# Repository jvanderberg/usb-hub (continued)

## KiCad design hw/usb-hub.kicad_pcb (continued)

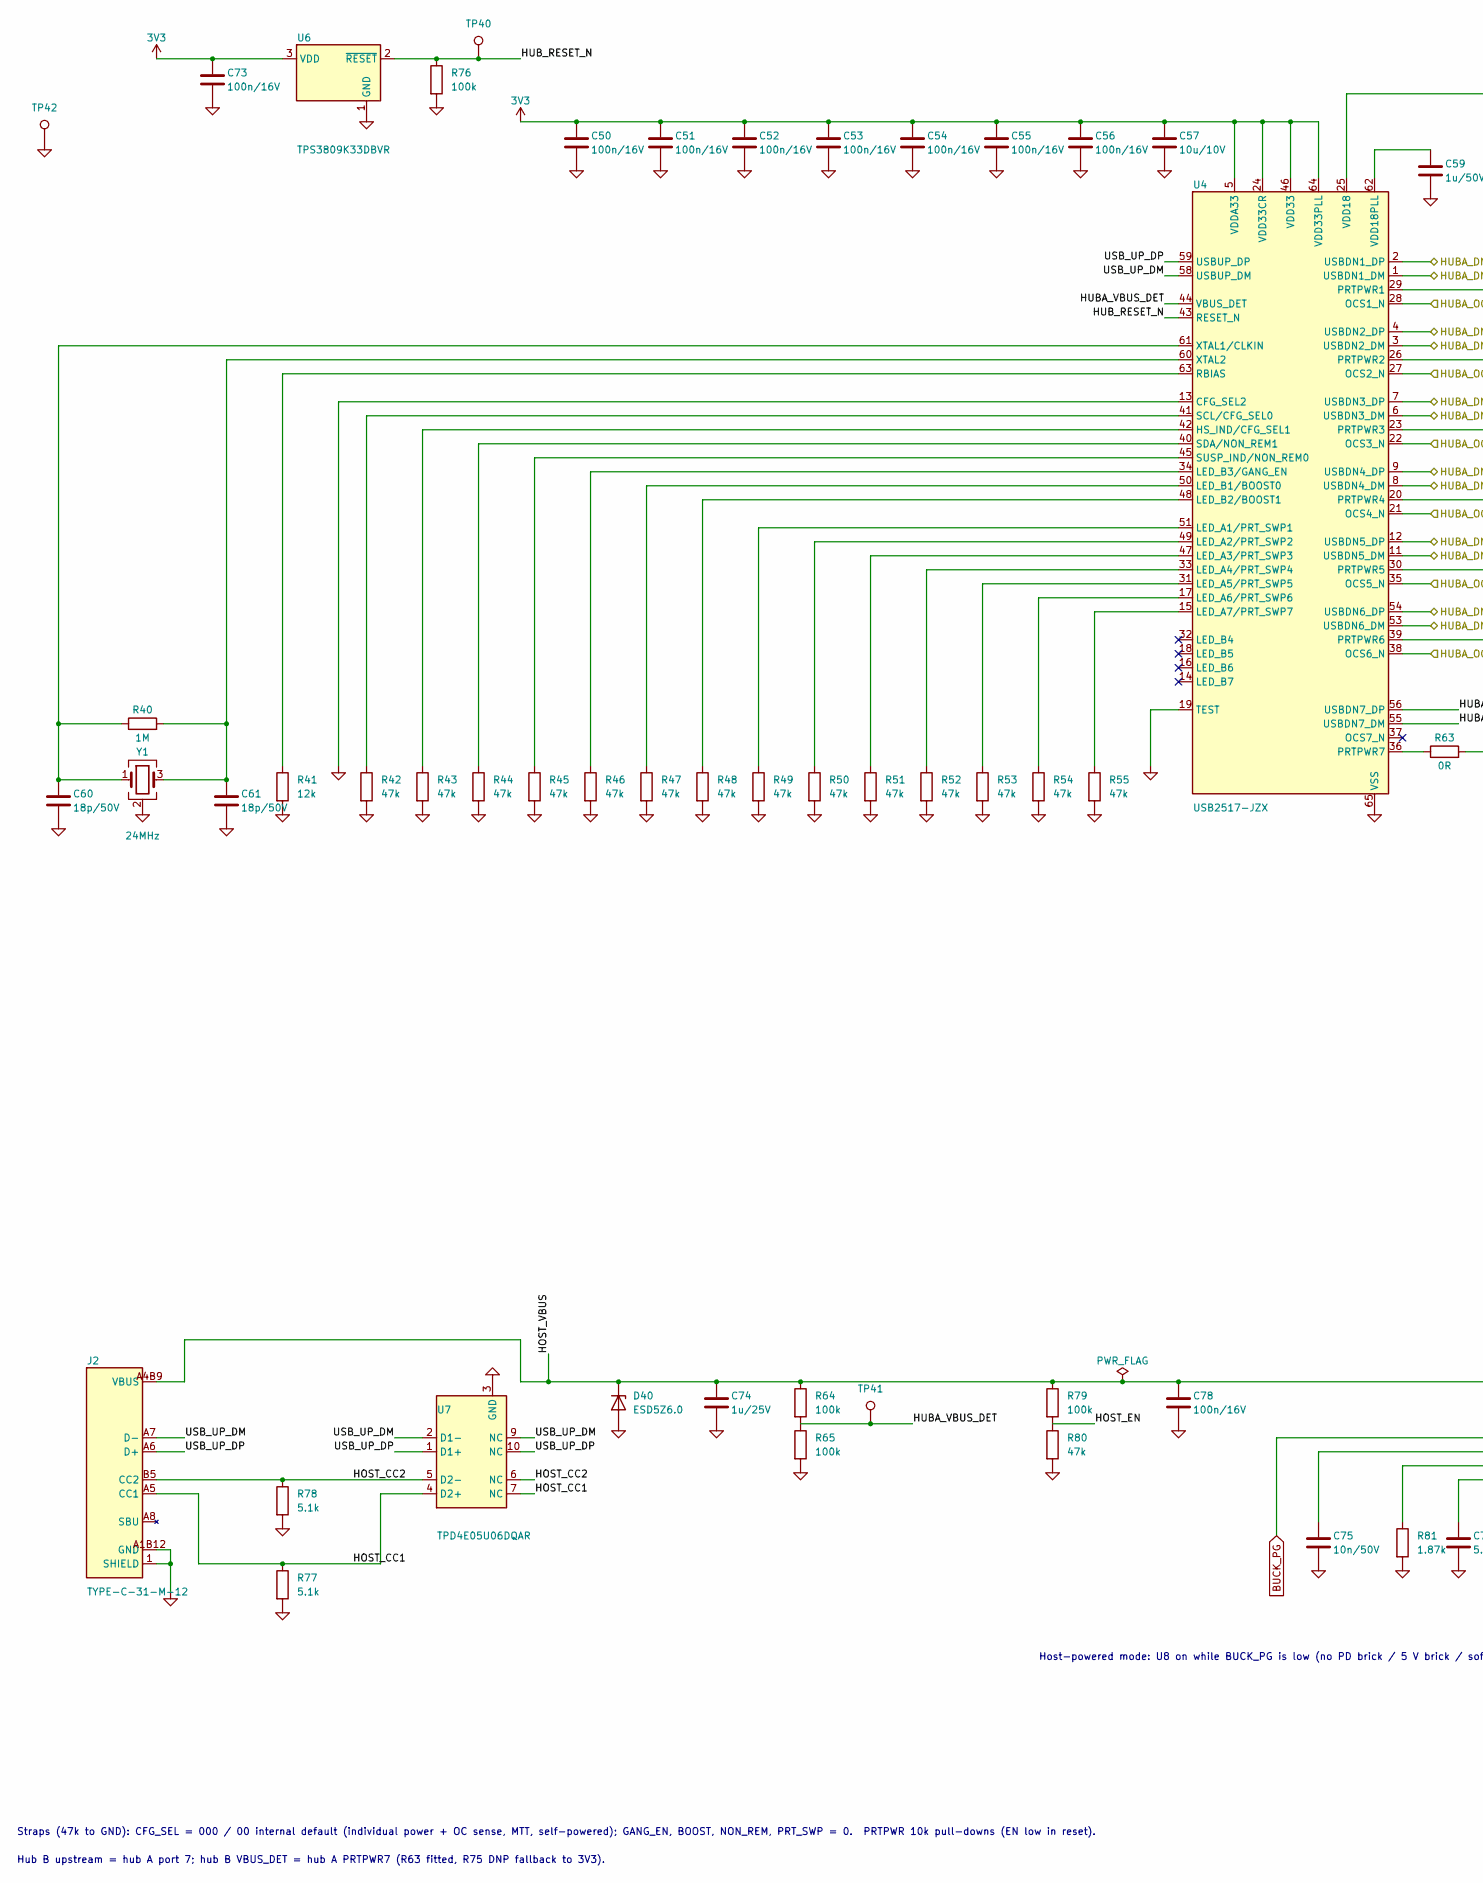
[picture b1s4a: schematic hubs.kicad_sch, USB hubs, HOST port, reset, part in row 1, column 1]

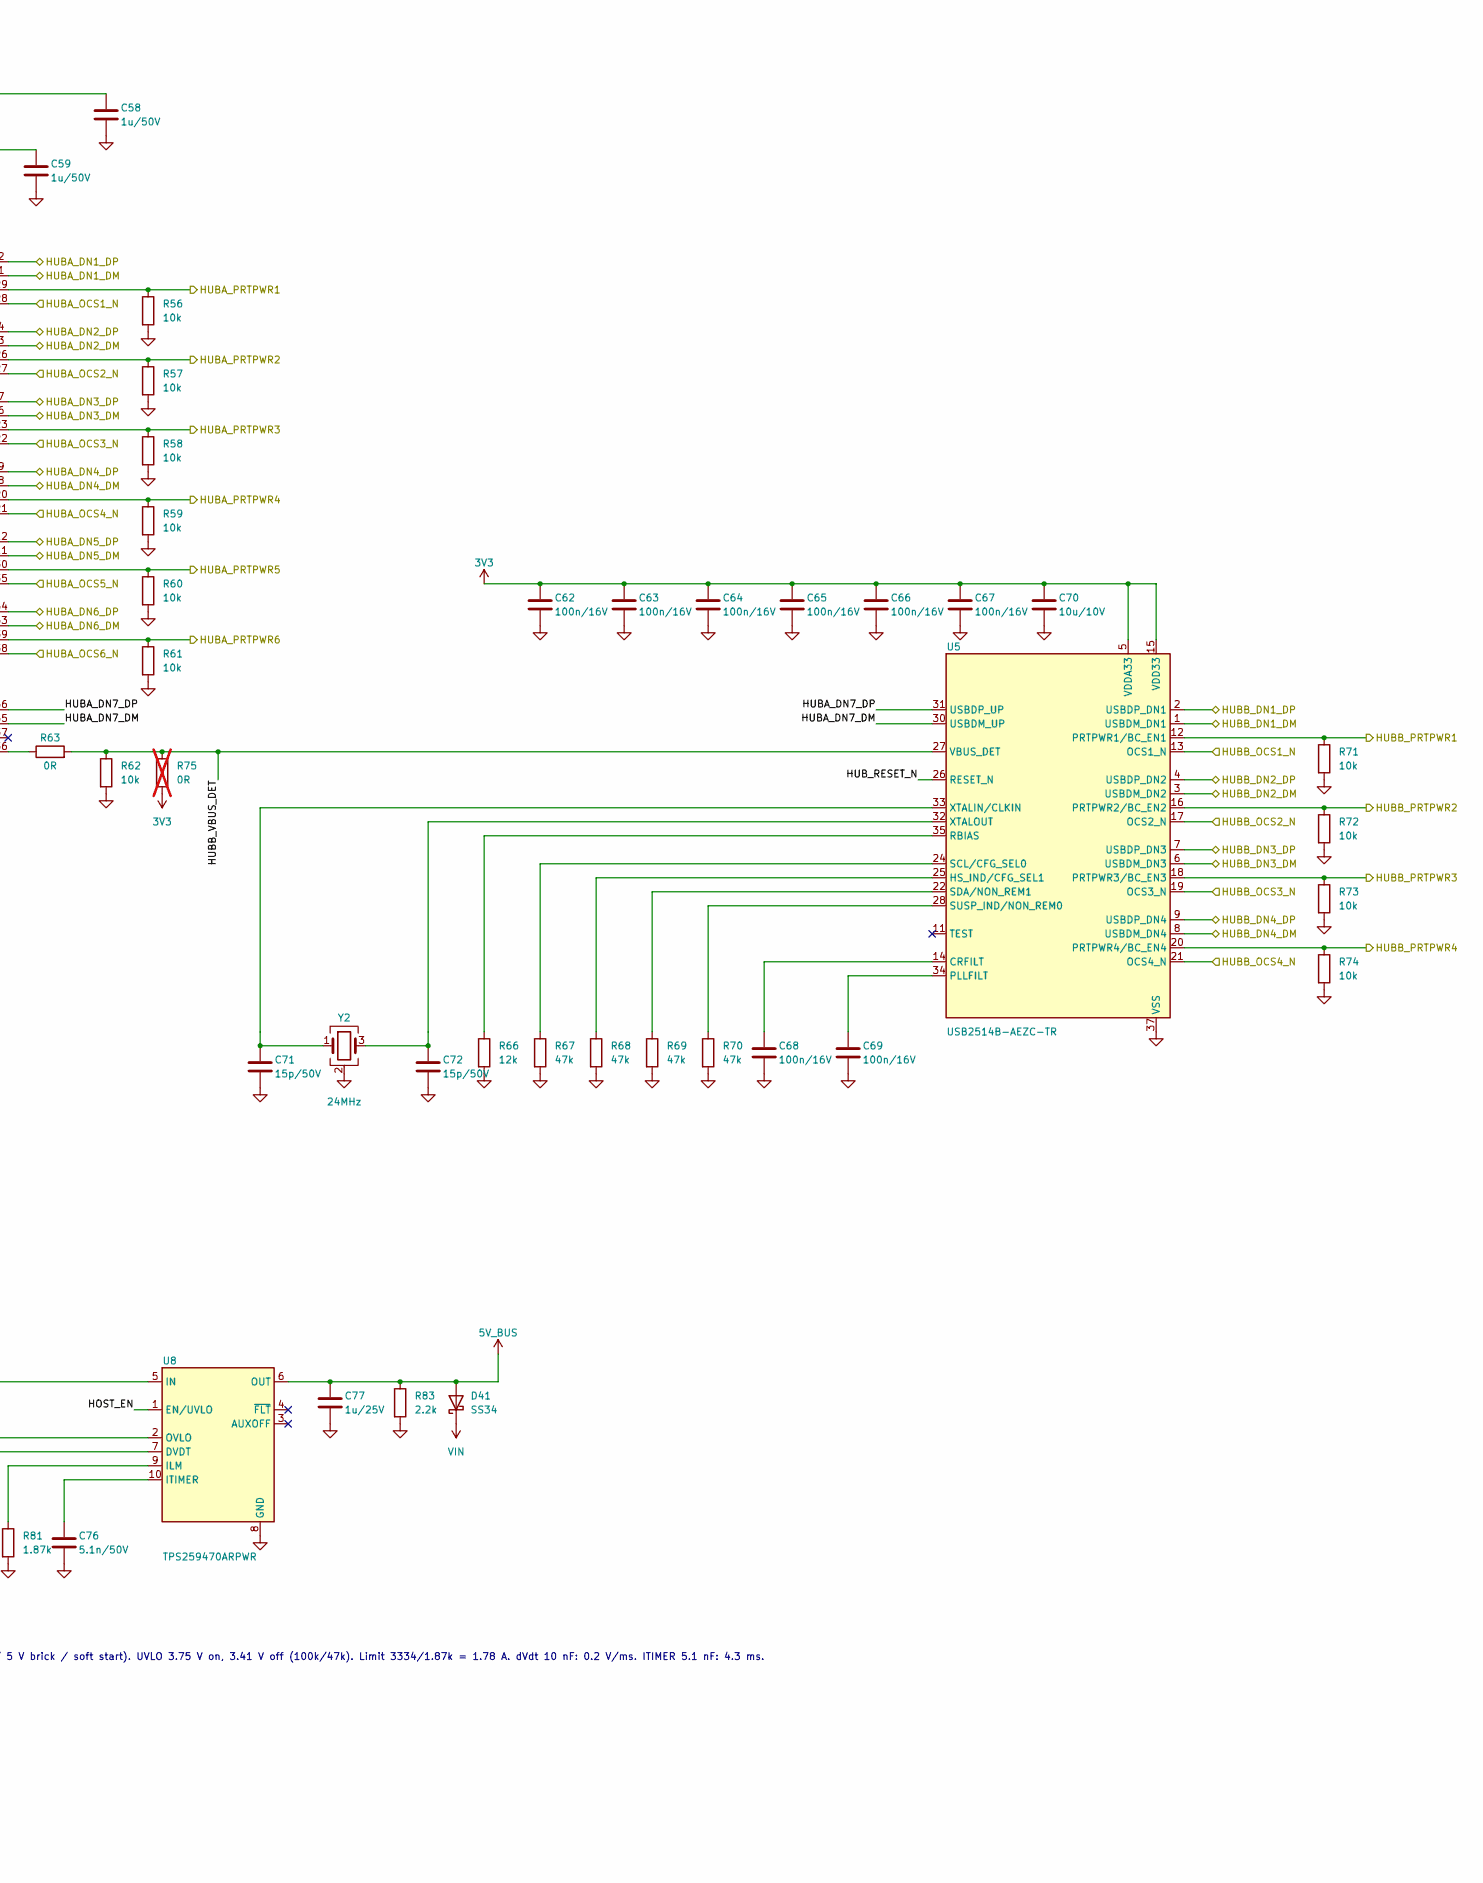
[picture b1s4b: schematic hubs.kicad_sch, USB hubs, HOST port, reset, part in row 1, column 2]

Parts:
C50, C51, C52, C53, C54, C55, C56, C62, C63, C64, C65, C66, C67, C68, C69, C73, C78: 100n/16V; CL05B104KO5NNNC; Manufacturer Part CL05B104KO5NNNC; LCSC C1525
C57, C70: 10u/10V; CL10A106KP8NNNC; Manufacturer Part CL10A106KP8NNNC; LCSC C19702
C58, C59: 1u/50V; CL10A105KB8NNNC; Manufacturer Part CL10A105KB8NNNC; LCSC C15849
C60, C61: 18p/50V; 0402CG180J500NT; Manufacturer Part 0402CG180J500NT; LCSC C1549
C71, C72: 15p/50V; 0402CG150J500NT; Manufacturer Part 0402CG150J500NT; LCSC C1548
C74, C77: 1u/25V; CL05A105KA5NQNC; Manufacturer Part CL05A105KA5NQNC; LCSC C52923
C75: 10n/50V; CL05B103KB5NNNC; Manufacturer Part CL05B103KB5NNNC; LCSC C15195
C76: 5.1n/50V; 0402B512K500NT; Manufacturer Part 0402B512K500NT; LCSC C47118429
D40: ESD5Z6.0; ESD5Z6_0T1G; Manufacturer Part ESD5Z6.0T1G; LCSC C82323
D41: SS34; SS34_C8678; Manufacturer Part SS34; LCSC C8678
J2: TYPE-C-31-M-12; Manufacturer Part TYPE-C-31-M-12; LCSC C165948
R40: 1M; 0402WGF1004TCE; Manufacturer Part 0402WGF1004TCE; LCSC C26083
R41, R66: 12k; 0402WGF1202TCE; Manufacturer Part 0402WGF1202TCE; LCSC C25752
R42, R43, R44, R45, R46, R47, R48, R49, R50, R51, R52, R53, R54, R55, R67, R68, R69, R70, R80: 47k; 0402WGF4702TCE; Manufacturer Part 0402WGF4702TCE; LCSC C25792
R56, R57, R58, R59, R60, R61, R62, R71, R72, R73, R74: 10k; 0402WGF1002TCE; Manufacturer Part 0402WGF1002TCE; LCSC C25744
R63: 0R; 0402WGF0000TCE; Manufacturer Part 0402WGF0000TCE; LCSC C17168
R64, R65, R76, R79: 100k; 0402WGF1003TCE; Manufacturer Part 0402WGF1003TCE; LCSC C25741
R75: 0R; 0402WGF0000TCE; Manufacturer Part 0402WGF0000TCE; LCSC C17168; not fitted
R77, R78: 5.1k; 0402WGF5101TCE; Manufacturer Part 0402WGF5101TCE; LCSC C25905
R81: 1.87k; 0402WGF1871TCE; Manufacturer Part 0402WGF1871TCE; LCSC C270633
R83: 2.2k; 0402WGF2201TCE; Manufacturer Part 0402WGF2201TCE; LCSC C25879
TP40: HUB_RESET_N; TestPoint_Pad_D1.0mm
TP41: VBUS_DET; TestPoint_Pad_D1.0mm
TP42: GND; TestPoint_Pad_D1.0mm
U4: USB2517-JZX; USB2517-JZX_ThermalVias; Manufacturer Part USB2517-JZX; LCSC C1521556
U5: USB2514B-AEZC-TR; USB2514B-AEZC-TR_ThermalVias; Manufacturer Part USB2514B-AEZC-TR; LCSC C16251
U6: TPS3809K33DBVR; Manufacturer Part TPS3809K33DBVR; LCSC C61364
U7: TPD4E05U06DQAR; TPD4E05U06DQAR_C138714; Manufacturer Part TPD4E05U06DQAR; LCSC C138714
U8: TPS259470ARPWR; TPS259470ARPWR_TILand; Manufacturer Part TPS259470ARPWR; LCSC C3662799
Y1, Y2: 24MHz; X322524MOB4SI; Manufacturer Part X322524MOB4SI; LCSC C70590

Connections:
3V3: C50.1, C51.1, C52.1, C53.1, C54.1, C55.1, C56.1, C57.1, C62.1, C63.1, C64.1, C65.1, C66.1, C67.1, C70.1, C73.1, R75.2, U4.5 (VDDA33), U4.10 (VDDA33), U4.24 (VDD33CR), U4.46 (VDD33), U4.52 (VDDA33), U4.57 (VDDA33), U4.64 (VDD33PLL), U5.5 (VDDA33), U5.10 (VDDA33), U5.15 (VDD33), U5.23 (VDD33), U5.29 (VDDA33), U5.36 (VDDA33), U6.3 (VDD); also elsewhere on the board
5V_BUS: C77.1, D41.2 (A), R83.1, U8.6 (OUT); also elsewhere on the board
/HUBA_DN1_DM: U4.1 (USBDN1_DM); also elsewhere on the board
/HUBA_DN1_DP: U4.2 (USBDN1_DP); also elsewhere on the board
/HUBA_DN2_DM: U4.3 (USBDN2_DM); also elsewhere on the board
/HUBA_DN2_DP: U4.4 (USBDN2_DP); also elsewhere on the board
/HUBA_DN3_DM: U4.6 (USBDN3_DM); also elsewhere on the board
/HUBA_DN3_DP: U4.7 (USBDN3_DP); also elsewhere on the board
/HUBA_DN4_DM: U4.8 (USBDN4_DM); also elsewhere on the board
/HUBA_DN4_DP: U4.9 (USBDN4_DP); also elsewhere on the board
/HUBA_DN5_DM: U4.11 (USBDN5_DM); also elsewhere on the board
/HUBA_DN5_DP: U4.12 (USBDN5_DP); also elsewhere on the board
/HUBA_DN6_DM: U4.53 (USBDN6_DM); also elsewhere on the board
/HUBA_DN6_DP: U4.54 (USBDN6_DP); also elsewhere on the board
/HUBA_OCS1_N: U4.28 (OCS1_N); also elsewhere on the board
/HUBA_OCS2_N: U4.27 (OCS2_N); also elsewhere on the board
/HUBA_OCS3_N: U4.22 (OCS3_N); also elsewhere on the board
/HUBA_OCS4_N: U4.21 (OCS4_N); also elsewhere on the board
/HUBA_OCS5_N: U4.35 (OCS5_N); also elsewhere on the board
/HUBA_OCS6_N: U4.38 (OCS6_N); also elsewhere on the board
/HUBA_PRTPWR1: R56.1, U4.29 (PRTPWR1); also elsewhere on the board
/HUBA_PRTPWR2: R57.1, U4.26 (PRTPWR2); also elsewhere on the board
/HUBA_PRTPWR3: R58.1, U4.23 (PRTPWR3); also elsewhere on the board
/HUBA_PRTPWR4: R59.1, U4.20 (PRTPWR4); also elsewhere on the board
/HUBA_PRTPWR5: R60.1, U4.30 (PRTPWR5); also elsewhere on the board
/HUBA_PRTPWR6: R61.1, U4.39 (PRTPWR6); also elsewhere on the board
/HUBB_DN1_DM: U5.1 (USBDM_DN1); also elsewhere on the board
/HUBB_DN1_DP: U5.2 (USBDP_DN1); also elsewhere on the board
/HUBB_DN2_DM: U5.3 (USBDM_DN2); also elsewhere on the board
/HUBB_DN2_DP: U5.4 (USBDP_DN2); also elsewhere on the board
/HUBB_DN3_DM: U5.6 (USBDM_DN3); also elsewhere on the board
/HUBB_DN3_DP: U5.7 (USBDP_DN3); also elsewhere on the board
/HUBB_DN4_DM: U5.8 (USBDM_DN4); also elsewhere on the board
/HUBB_DN4_DP: U5.9 (USBDP_DN4); also elsewhere on the board
/HUBB_OCS1_N: U5.13 (OCS1_N); also elsewhere on the board
/HUBB_OCS2_N: U5.17 (OCS2_N); also elsewhere on the board
/HUBB_OCS3_N: U5.19 (OCS3_N); also elsewhere on the board
/HUBB_OCS4_N: U5.21 (OCS4_N); also elsewhere on the board
/HUBB_PRTPWR1: R71.1, U5.12 (PRTPWR1/BC_EN1); also elsewhere on the board
/HUBB_PRTPWR2: R72.1, U5.16 (PRTPWR2/BC_EN2); also elsewhere on the board
/HUBB_PRTPWR3: R73.1, U5.18 (PRTPWR3/BC_EN3); also elsewhere on the board
/HUBB_PRTPWR4: R74.1, U5.20 (PRTPWR4/BC_EN4); also elsewhere on the board
/hubs/HOST_CC1: J2.A5 (CC1), R77.1, U7.4 (D2+), U7.7 (NC)
/hubs/HOST_CC2: J2.B5 (CC2), R78.1, U7.5 (D2-), U7.6 (NC)
/hubs/HOST_EN: R79.2, R80.1, U8.1 (EN/UVLO)
/hubs/HOST_VBUS: C74.1, C78.1, D40.1 (K), J2.A4B9 (VBUS), J2.B4A9 (VBUS), R64.1, R79.1, U8.5 (IN)
/hubs/HUBA_DN7_DM: U4.55 (USBDN7_DM), U5.30 (USBDM_UP)
/hubs/HUBA_DN7_DP: U4.56 (USBDN7_DP), U5.31 (USBDP_UP)
/hubs/HUBA_VBUS_DET: R64.2, R65.1, TP41.1 (1_1), U4.44 (VBUS_DET)
/hubs/HUBB_VBUS_DET: R62.1, R63.2, R75.1, U5.27 (VBUS_DET)
/hubs/HUB_RESET_N: R76.1, TP40.1 (1_1), U4.43 (RESET_N), U5.26 (RESET_N), U6.2 (~RESET)
/hubs/USB_UP_DM: J2.A7 (D-), J2.B7 (D-), U4.58 (USBUP_DM), U7.2 (D1-), U7.9 (NC)
/hubs/USB_UP_DP: J2.A6 (D+), J2.B6 (D+), U4.59 (USBUP_DP), U7.1 (D1+), U7.10 (NC)
BUCK_PG: U8.2 (OVLO); also elsewhere on the board
GND: C50.2, C51.2, C52.2, C53.2, C54.2, C55.2, C56.2, C57.2, C58.2, C59.2, C60.2, C61.2, C62.2, C63.2, C64.2, C65.2, C66.2, C67.2, C68.2, C69.2, C70.2, C71.2, C72.2, C73.2, C74.2, C75.2, C76.2, C77.2, C78.2, D40.2 (A), J2.1 (SHIELD), J2.2 (SHIELD), J2.3 (SHIELD), J2.4 (SHIELD), J2.A1B12 (GND), J2.B1A12 (GND), R41.2, R42.2, R43.2, R44.2, R45.2, R46.2, R47.2, R48.2, R49.2, R50.2, R51.2, R52.2, R53.2, R54.2, R55.2, R56.2, R57.2, R58.2, R59.2, R60.2, R61.2, R62.2, R65.2, R66.2, R67.2, R68.2, R69.2, R70.2, R71.2, R72.2, R73.2, R74.2, R76.2, R77.2, R78.2, R80.2, R81.2, R83.2, TP42.1 (1_1), U4.13 (CFG_SEL2), U4.19 (TEST), U4.65 (VSS), U5.37 (VSS), U6.1 (GND), U7.3 (GND), U7.8 (GND), U8.8 (GND), Y1.2 (G), Y1.4 (G), Y2.2 (G), Y2.4 (G); also elsewhere on the board
unnamed: R43.1, U4.42 (HS_IND/CFG_SEL1)
unnamed: R49.1, U4.51 (LED_A1/PRT_SWP1)
unnamed: R50.1, U4.49 (LED_A2/PRT_SWP2)
unnamed: R51.1, U4.47 (LED_A3/PRT_SWP3)
unnamed: R52.1, U4.33 (LED_A4/PRT_SWP4)
unnamed: R53.1, U4.31 (LED_A5/PRT_SWP5)
unnamed: R54.1, U4.17 (LED_A6/PRT_SWP6)
unnamed: R55.1, U4.15 (LED_A7/PRT_SWP7)
unnamed: R47.1, U4.50 (LED_B1/BOOST0)
unnamed: R48.1, U4.48 (LED_B2/BOOST1)
unnamed: R46.1, U4.34 (LED_B3/GANG_EN)
unnamed: R63.1, U4.36 (PRTPWR7)
unnamed: R41.1, U4.63 (RBIAS)
unnamed: R42.1, U4.41 (SCL/CFG_SEL0)
unnamed: R44.1, U4.40 (SDA/NON_REM1)
unnamed: R45.1, U4.45 (SUSP_IND/NON_REM0)
unnamed: C58.1, U4.25 (VDD18)
unnamed: C59.1, U4.62 (VDD18PLL)
unnamed: C60.1, R40.1, U4.61 (XTAL1/CLKIN), Y1.1
unnamed: C61.1, R40.2, U4.60 (XTAL2), Y1.3
unnamed: C68.1, U5.14 (CRFILT)
unnamed: R68.1, U5.25 (HS_IND/CFG_SEL1)
unnamed: C69.1, U5.34 (PLLFILT)
unnamed: R66.1, U5.35 (RBIAS)
unnamed: R67.1, U5.24 (SCL/CFG_SEL0)
unnamed: R69.1, U5.22 (SDA/NON_REM1)
unnamed: R70.1, U5.28 (SUSP_IND/NON_REM0)
unnamed: C71.1, U5.33 (XTALIN/CLKIN), Y2.1
unnamed: C72.1, U5.32 (XTALOUT), Y2.3
unnamed: C75.1, U8.7 (DVDT)
unnamed: R81.1, U8.9 (ILM)
unnamed: C76.1, U8.10 (ITIMER)
VIN: D41.1 (K); also elsewhere on the board

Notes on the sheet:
Host-powered mode: U8 on while BUCK_PG is low (no PD brick / 5 V brick / soft start). UVLO 3.75 V on, 3.41 V off (100k/47k). Limit 3334/1.87k = 1.78 A. dVdt 10 nF: 0.2 V/ms. ITIMER 5.1 nF: 4.3 ms.
Straps (47k to GND): CFG_SEL = 000 / 00 internal default (individual power + OC sense, MTT, self-powered); GANG_EN, BOOST, NON_REM, PRT_SWP = 0. PRTPWR 10k pull-downs (EN low in reset).
Hub B upstream = hub A port 7; hub B VBUS_DET = hub A PRTPWR7 (R63 fitted, R75 DNP fallback to 3V3).

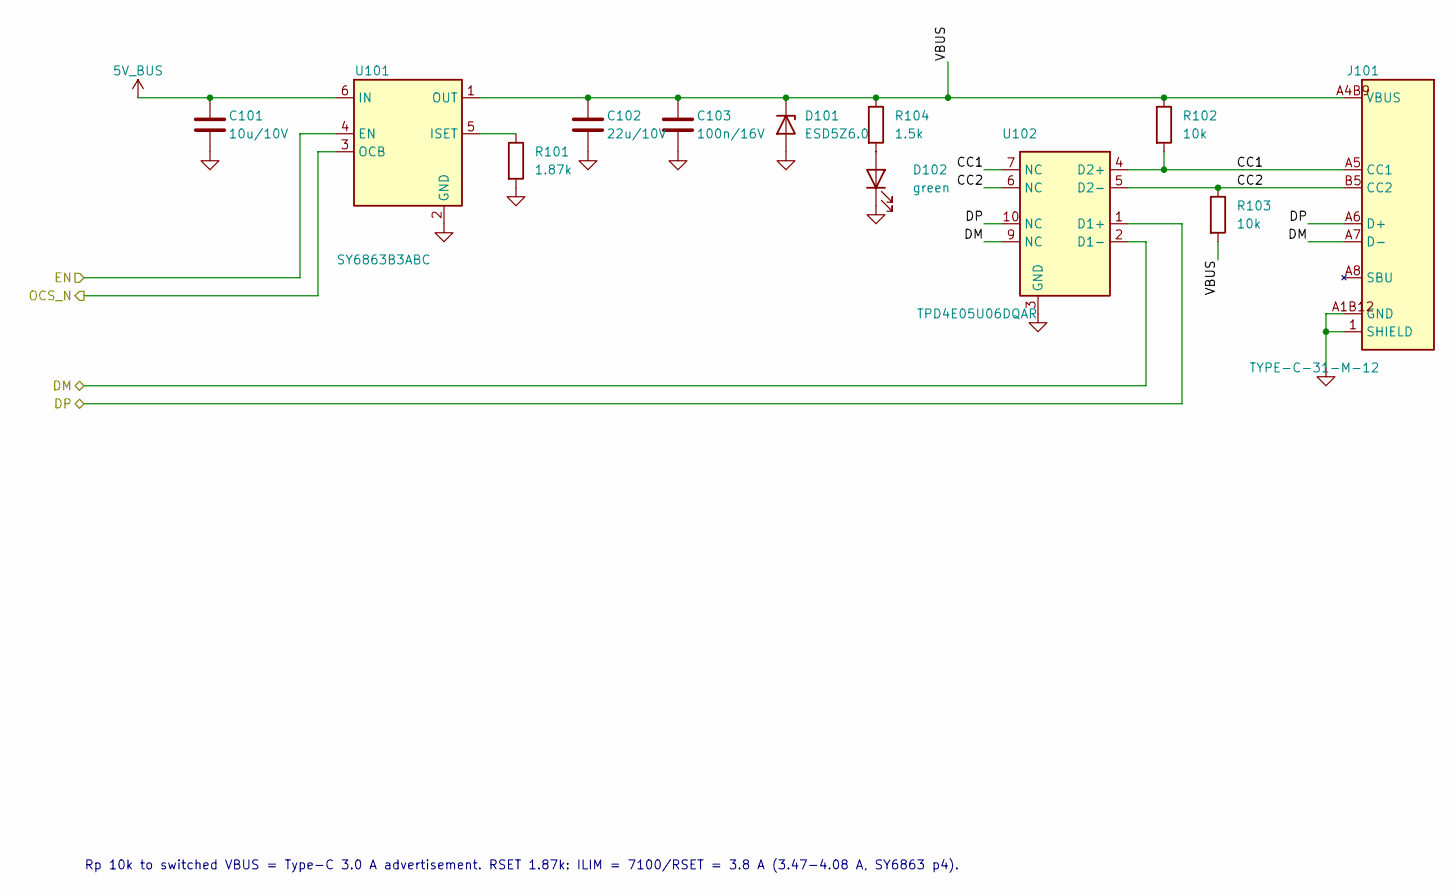
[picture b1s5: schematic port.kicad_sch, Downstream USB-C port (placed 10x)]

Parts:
C101: 10u/10V; CL10A106KP8NNNC; Manufacturer Part CL10A106KP8NNNC; LCSC C19702
C102: 22u/10V; CL10A226MQ8NRNC; Manufacturer Part CL10A226MQ8NRNC; LCSC C59461
C103: 100n/16V; CL05B104KO5NNNC; Manufacturer Part CL05B104KO5NNNC; LCSC C1525
D101: ESD5Z6.0; ESD5Z6_0T1G; Manufacturer Part ESD5Z6.0T1G; LCSC C82323
D102: green; 0603_Green_509-620mcd; Manufacturer Part KT-0603G; LCSC C12624
J101: TYPE-C-31-M-12; Manufacturer Part TYPE-C-31-M-12; LCSC C165948
R101: 1.87k; 0402WGF1871TCE; Manufacturer Part 0402WGF1871TCE; LCSC C270633
R102, R103: 10k; 0402WGF1002TCE; Manufacturer Part 0402WGF1002TCE; LCSC C25744
R104: 1.5k; 0402WGF1501TCE; Manufacturer Part 0402WGF1501TCE; LCSC C25867
U101: SY6863B3ABC; Manufacturer Part SY6863B3ABC; LCSC C2687365
U102: TPD4E05U06DQAR; TPD4E05U06DQAR_C138714; Manufacturer Part TPD4E05U06DQAR; LCSC C138714

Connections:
5V_BUS: C101.1, U101.6 (IN); also elsewhere on the board
/HUBA_DN1_DM: J101.A7 (D-), J101.B7 (D-), U102.2 (D1-), U102.9 (NC); also elsewhere on the board
/HUBA_DN1_DP: J101.A6 (D+), J101.B6 (D+), U102.1 (D1+), U102.10 (NC); also elsewhere on the board
/HUBA_OCS1_N: U101.3 (OCB); also elsewhere on the board
/HUBA_PRTPWR1: U101.4 (EN); also elsewhere on the board
/port1/CC1: J101.A5 (CC1), R102.2, U102.4 (D2+), U102.7 (NC)
/port1/CC2: J101.B5 (CC2), R103.1, U102.5 (D2-), U102.6 (NC)
/port1/VBUS: C102.1, C103.1, D101.1 (K), J101.A4B9 (VBUS), J101.B4A9 (VBUS), R102.1, R103.2, R104.1, U101.1 (OUT)
GND: C101.2, C102.2, C103.2, D101.2 (A), D102.1 (K), J101.1 (SHIELD), J101.2 (SHIELD), J101.3 (SHIELD), J101.4 (SHIELD), J101.A1B12 (GND), J101.B1A12 (GND), R101.2, U101.2 (GND), U102.3 (GND), U102.8 (GND); also elsewhere on the board
unnamed: D102.2 (A), R104.2
unnamed: R101.1, U101.5 (ISET)

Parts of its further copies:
C201, C301, C401, C501, C601, C701, C801, C901, C1001: 10u/10V; CL10A106KP8NNNC; Manufacturer Part CL10A106KP8NNNC; LCSC C19702
C202, C302, C402, C502, C602, C702, C802, C902, C1002: 22u/10V; CL10A226MQ8NRNC; Manufacturer Part CL10A226MQ8NRNC; LCSC C59461
C203, C303, C403, C503, C603, C703, C803, C903, C1003: 100n/16V; CL05B104KO5NNNC; Manufacturer Part CL05B104KO5NNNC; LCSC C1525
D201, D301, D401, D501, D601, D701, D801, D901, D1001: ESD5Z6.0; ESD5Z6_0T1G; Manufacturer Part ESD5Z6.0T1G; LCSC C82323
D202, D302, D402, D502, D602, D702, D802, D902, D1002: green; 0603_Green_509-620mcd; Manufacturer Part KT-0603G; LCSC C12624
J201, J301, J401, J501, J601, J701, J801, J901, J1001: TYPE-C-31-M-12; Manufacturer Part TYPE-C-31-M-12; LCSC C165948
R201, R301, R401, R501, R601, R701, R801, R901, R1001: 1.87k; 0402WGF1871TCE; Manufacturer Part 0402WGF1871TCE; LCSC C270633
R202, R203, R302, R303, R402, R403, R502, R503, R602, R603, R702, R703, R802, R803, R902, R903, R1002, R1003: 10k; 0402WGF1002TCE; Manufacturer Part 0402WGF1002TCE; LCSC C25744
R204, R304, R404, R504, R604, R704, R804, R904, R1004: 1.5k; 0402WGF1501TCE; Manufacturer Part 0402WGF1501TCE; LCSC C25867
U201, U301, U401, U501, U601, U701, U801, U901, U1001: SY6863B3ABC; Manufacturer Part SY6863B3ABC; LCSC C2687365
U202, U302, U402, U502, U602, U702, U802, U902, U1002: TPD4E05U06DQAR; TPD4E05U06DQAR_C138714; Manufacturer Part TPD4E05U06DQAR; LCSC C138714

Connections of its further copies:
5V_BUS: C201.1, C301.1, C401.1, C501.1, C601.1, C701.1, C801.1, C901.1, C1001.1, U201.6 (IN), U301.6 (IN), U401.6 (IN), U501.6 (IN), U601.6 (IN), U701.6 (IN), U801.6 (IN), U901.6 (IN), U1001.6 (IN); also elsewhere on the board
/HUBA_DN2_DM: J201.A7 (D-), J201.B7 (D-), U202.2 (D1-), U202.9 (NC); also elsewhere on the board
/HUBA_DN2_DP: J201.A6 (D+), J201.B6 (D+), U202.1 (D1+), U202.10 (NC); also elsewhere on the board
/HUBA_DN3_DM: J301.A7 (D-), J301.B7 (D-), U302.2 (D1-), U302.9 (NC); also elsewhere on the board
/HUBA_DN3_DP: J301.A6 (D+), J301.B6 (D+), U302.1 (D1+), U302.10 (NC); also elsewhere on the board
/HUBA_DN4_DM: J401.A7 (D-), J401.B7 (D-), U402.2 (D1-), U402.9 (NC); also elsewhere on the board
/HUBA_DN4_DP: J401.A6 (D+), J401.B6 (D+), U402.1 (D1+), U402.10 (NC); also elsewhere on the board
/HUBA_DN5_DM: J501.A7 (D-), J501.B7 (D-), U502.2 (D1-), U502.9 (NC); also elsewhere on the board
/HUBA_DN5_DP: J501.A6 (D+), J501.B6 (D+), U502.1 (D1+), U502.10 (NC); also elsewhere on the board
/HUBA_DN6_DM: J601.A7 (D-), J601.B7 (D-), U602.2 (D1-), U602.9 (NC); also elsewhere on the board
/HUBA_DN6_DP: J601.A6 (D+), J601.B6 (D+), U602.1 (D1+), U602.10 (NC); also elsewhere on the board
/HUBA_OCS2_N: U201.3 (OCB); also elsewhere on the board
/HUBA_OCS3_N: U301.3 (OCB); also elsewhere on the board
/HUBA_OCS4_N: U401.3 (OCB); also elsewhere on the board
/HUBA_OCS5_N: U501.3 (OCB); also elsewhere on the board
/HUBA_OCS6_N: U601.3 (OCB); also elsewhere on the board
/HUBA_PRTPWR2: U201.4 (EN); also elsewhere on the board
/HUBA_PRTPWR3: U301.4 (EN); also elsewhere on the board
/HUBA_PRTPWR4: U401.4 (EN); also elsewhere on the board
/HUBA_PRTPWR5: U501.4 (EN); also elsewhere on the board
/HUBA_PRTPWR6: U601.4 (EN); also elsewhere on the board
/HUBB_DN1_DM: J701.A7 (D-), J701.B7 (D-), U702.2 (D1-), U702.9 (NC); also elsewhere on the board
/HUBB_DN1_DP: J701.A6 (D+), J701.B6 (D+), U702.1 (D1+), U702.10 (NC); also elsewhere on the board
/HUBB_DN2_DM: J801.A7 (D-), J801.B7 (D-), U802.2 (D1-), U802.9 (NC); also elsewhere on the board
/HUBB_DN2_DP: J801.A6 (D+), J801.B6 (D+), U802.1 (D1+), U802.10 (NC); also elsewhere on the board
/HUBB_DN3_DM: J901.A7 (D-), J901.B7 (D-), U902.2 (D1-), U902.9 (NC); also elsewhere on the board
/HUBB_DN3_DP: J901.A6 (D+), J901.B6 (D+), U902.1 (D1+), U902.10 (NC); also elsewhere on the board
/HUBB_DN4_DM: J1001.A7 (D-), J1001.B7 (D-), U1002.2 (D1-), U1002.9 (NC); also elsewhere on the board
/HUBB_DN4_DP: J1001.A6 (D+), J1001.B6 (D+), U1002.1 (D1+), U1002.10 (NC); also elsewhere on the board
/HUBB_OCS1_N: U701.3 (OCB); also elsewhere on the board
/HUBB_OCS2_N: U801.3 (OCB); also elsewhere on the board
/HUBB_OCS3_N: U901.3 (OCB); also elsewhere on the board
/HUBB_OCS4_N: U1001.3 (OCB); also elsewhere on the board
/HUBB_PRTPWR1: U701.4 (EN); also elsewhere on the board
/HUBB_PRTPWR2: U801.4 (EN); also elsewhere on the board
/HUBB_PRTPWR3: U901.4 (EN); also elsewhere on the board
/HUBB_PRTPWR4: U1001.4 (EN); also elsewhere on the board
/port2/CC1: J201.A5 (CC1), R202.2, U202.4 (D2+), U202.7 (NC)
/port2/CC2: J201.B5 (CC2), R203.1, U202.5 (D2-), U202.6 (NC)
/port2/VBUS: C202.1, C203.1, D201.1 (K), J201.A4B9 (VBUS), J201.B4A9 (VBUS), R202.1, R203.2, R204.1, U201.1 (OUT)
/port3/CC1: J301.A5 (CC1), R302.2, U302.4 (D2+), U302.7 (NC)
/port3/CC2: J301.B5 (CC2), R303.1, U302.5 (D2-), U302.6 (NC)
/port3/VBUS: C302.1, C303.1, D301.1 (K), J301.A4B9 (VBUS), J301.B4A9 (VBUS), R302.1, R303.2, R304.1, U301.1 (OUT)
/port4/CC1: J401.A5 (CC1), R402.2, U402.4 (D2+), U402.7 (NC)
/port4/CC2: J401.B5 (CC2), R403.1, U402.5 (D2-), U402.6 (NC)
/port4/VBUS: C402.1, C403.1, D401.1 (K), J401.A4B9 (VBUS), J401.B4A9 (VBUS), R402.1, R403.2, R404.1, U401.1 (OUT)
/port5/CC1: J501.A5 (CC1), R502.2, U502.4 (D2+), U502.7 (NC)
/port5/CC2: J501.B5 (CC2), R503.1, U502.5 (D2-), U502.6 (NC)
/port5/VBUS: C502.1, C503.1, D501.1 (K), J501.A4B9 (VBUS), J501.B4A9 (VBUS), R502.1, R503.2, R504.1, U501.1 (OUT)
/port6/CC1: J601.A5 (CC1), R602.2, U602.4 (D2+), U602.7 (NC)
/port6/CC2: J601.B5 (CC2), R603.1, U602.5 (D2-), U602.6 (NC)
/port6/VBUS: C602.1, C603.1, D601.1 (K), J601.A4B9 (VBUS), J601.B4A9 (VBUS), R602.1, R603.2, R604.1, U601.1 (OUT)
/port7/CC1: J701.A5 (CC1), R702.2, U702.4 (D2+), U702.7 (NC)
/port7/CC2: J701.B5 (CC2), R703.1, U702.5 (D2-), U702.6 (NC)
/port7/VBUS: C702.1, C703.1, D701.1 (K), J701.A4B9 (VBUS), J701.B4A9 (VBUS), R702.1, R703.2, R704.1, U701.1 (OUT)
/port8/CC1: J801.A5 (CC1), R802.2, U802.4 (D2+), U802.7 (NC)
/port8/CC2: J801.B5 (CC2), R803.1, U802.5 (D2-), U802.6 (NC)
/port8/VBUS: C802.1, C803.1, D801.1 (K), J801.A4B9 (VBUS), J801.B4A9 (VBUS), R802.1, R803.2, R804.1, U801.1 (OUT)
/port9/CC1: J901.A5 (CC1), R902.2, U902.4 (D2+), U902.7 (NC)
/port9/CC2: J901.B5 (CC2), R903.1, U902.5 (D2-), U902.6 (NC)
/port9/VBUS: C902.1, C903.1, D901.1 (K), J901.A4B9 (VBUS), J901.B4A9 (VBUS), R902.1, R903.2, R904.1, U901.1 (OUT)
/port10/CC1: J1001.A5 (CC1), R1002.2, U1002.4 (D2+), U1002.7 (NC)
/port10/CC2: J1001.B5 (CC2), R1003.1, U1002.5 (D2-), U1002.6 (NC)
/port10/VBUS: C1002.1, C1003.1, D1001.1 (K), J1001.A4B9 (VBUS), J1001.B4A9 (VBUS), R1002.1, R1003.2, R1004.1, U1001.1 (OUT)
GND: C201.2, C202.2, C203.2, C301.2, C302.2, C303.2, C401.2, C402.2, C403.2, C501.2, C502.2, C503.2, C601.2, C602.2, C603.2, C701.2, C702.2, C703.2, C801.2, C802.2, C803.2, C901.2, C902.2, C903.2, C1001.2, C1002.2, C1003.2, D201.2 (A), D202.1 (K), D301.2 (A), D302.1 (K), D401.2 (A), D402.1 (K), D501.2 (A), D502.1 (K), D601.2 (A), D602.1 (K), D701.2 (A), D702.1 (K), D801.2 (A), D802.1 (K), D901.2 (A), D902.1 (K), D1001.2 (A), D1002.1 (K), J201.1 (SHIELD), J201.2 (SHIELD), J201.3 (SHIELD), J201.4 (SHIELD), J201.A1B12 (GND), J201.B1A12 (GND), J301.1 (SHIELD), J301.2 (SHIELD), J301.3 (SHIELD), J301.4 (SHIELD), J301.A1B12 (GND), J301.B1A12 (GND), J401.1 (SHIELD), J401.2 (SHIELD), J401.3 (SHIELD), J401.4 (SHIELD), J401.A1B12 (GND), J401.B1A12 (GND), J501.1 (SHIELD), J501.2 (SHIELD), J501.3 (SHIELD), J501.4 (SHIELD), J501.A1B12 (GND), J501.B1A12 (GND), J601.1 (SHIELD), J601.2 (SHIELD), J601.3 (SHIELD), J601.4 (SHIELD), J601.A1B12 (GND), J601.B1A12 (GND), J701.1 (SHIELD), J701.2 (SHIELD), J701.3 (SHIELD), J701.4 (SHIELD), J701.A1B12 (GND), J701.B1A12 (GND), J801.1 (SHIELD), J801.2 (SHIELD), J801.3 (SHIELD), J801.4 (SHIELD), J801.A1B12 (GND), J801.B1A12 (GND), J901.1 (SHIELD), J901.2 (SHIELD), J901.3 (SHIELD), J901.4 (SHIELD), J901.A1B12 (GND), J901.B1A12 (GND), J1001.1 (SHIELD), J1001.2 (SHIELD), J1001.3 (SHIELD), J1001.4 (SHIELD), J1001.A1B12 (GND), J1001.B1A12 (GND), R201.2, R301.2, R401.2, R501.2, R601.2, R701.2, R801.2, R901.2, R1001.2, U201.2 (GND), U202.3 (GND), U202.8 (GND), U301.2 (GND), U302.3 (GND), U302.8 (GND), U401.2 (GND), U402.3 (GND), U402.8 (GND), U501.2 (GND), U502.3 (GND), U502.8 (GND), U601.2 (GND), U602.3 (GND), U602.8 (GND), U701.2 (GND), U702.3 (GND), U702.8 (GND), U801.2 (GND), U802.3 (GND), U802.8 (GND), U901.2 (GND), U902.3 (GND), U902.8 (GND), U1001.2 (GND), U1002.3 (GND), U1002.8 (GND); also elsewhere on the board
unnamed: D202.2 (A), R204.2
unnamed: D302.2 (A), R304.2
unnamed: D402.2 (A), R404.2
unnamed: D502.2 (A), R504.2
unnamed: D602.2 (A), R604.2
unnamed: D702.2 (A), R704.2
unnamed: D802.2 (A), R804.2
unnamed: D902.2 (A), R904.2
unnamed: D1002.2 (A), R1004.2
unnamed: R201.1, U201.5 (ISET)
unnamed: R301.1, U301.5 (ISET)
unnamed: R401.1, U401.5 (ISET)
unnamed: R501.1, U501.5 (ISET)
unnamed: R601.1, U601.5 (ISET)
unnamed: R701.1, U701.5 (ISET)
unnamed: R801.1, U801.5 (ISET)
unnamed: R901.1, U901.5 (ISET)
unnamed: R1001.1, U1001.5 (ISET)

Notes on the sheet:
Rp 10k to switched VBUS = Type-C 3.0 A advertisement. RSET 1.87k: ILIM = 7100/RSET = 3.8 A (3.47-4.08 A, SY6863 p4).

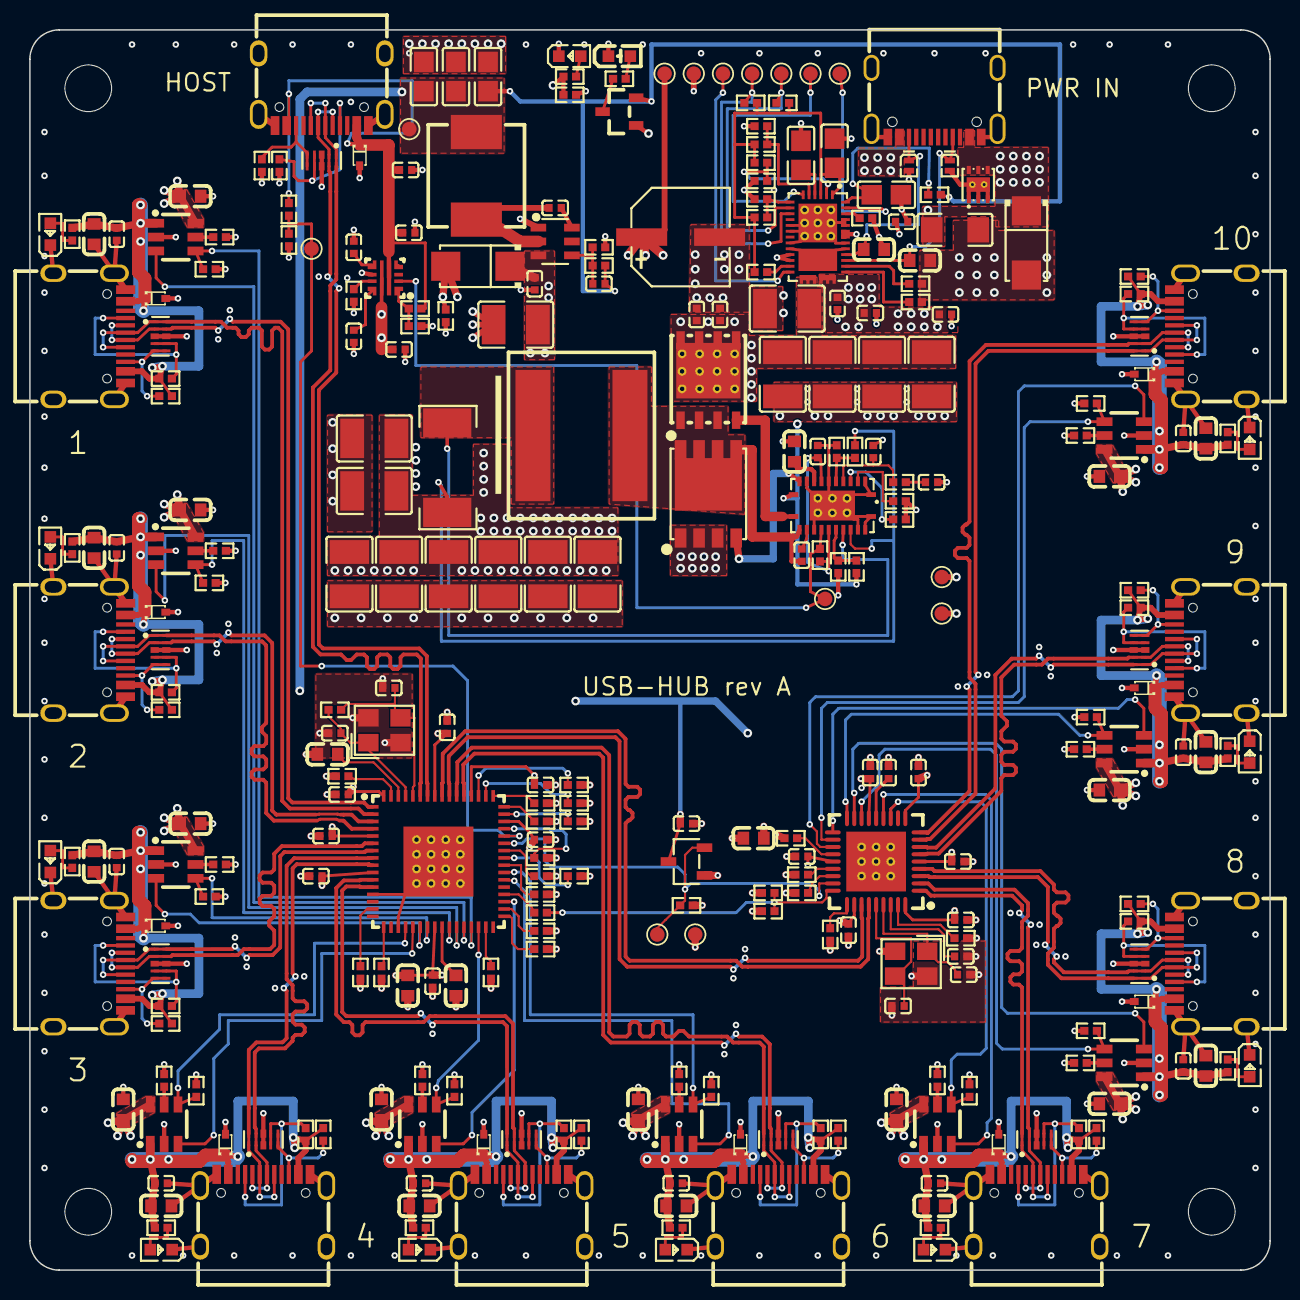
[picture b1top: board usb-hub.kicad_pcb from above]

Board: 4 copper layers, 85.0 x 85.0 mm, 300 parts (0 on the bottom side), 176 nets.

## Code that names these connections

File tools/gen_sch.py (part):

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    f = flag(s, 193.04, yv)
    s.tap(f.p(1))
    s.wire((205.74, yv), (205.74, yv - 5.08))
    s.label('PD_VBUS', 205.74, yv - 5.08, 90)
    # CC1 straight; CC2 dips under CC1's shunts (no crossings)
    xa, xb = xJ + 7.62, xJ + 55.88
    s.wire(J.p('A5'), U.p('28'))
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             (U.p('19'), br_tp('TP5', 'SINK_EN')),
             (U.p('6'), br_tp('TP6', 'CAP_MIS')),
             (U.p('37'), br_tp('TP7', 'PLUG_EVENT')),
             (U.p('15'), br_label('PD_DRAIN'))]
    xrr = bank(s, rrows, xr + 86.36, yb, side="R")
    for p in ('13', '10'):
        s.nc(U.p(p))
    x_rail_r = xrr[0] + 15.24                    # C9 item's drop to the rail
    s.wire((xl[0] - 5.08, yr), (x_rail_r, yr))
    s.label('PD_LDO3V3', xl[0] - 5.08, yr, 180)
    # VIN: PPHV up and along above the right bank: local cap, bulk, test pad
    pp = U.p('20')
    yvin = snap(pp[1] - 20.32)
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            (U.p('8'), item(br_part('C', 'C45', 'C1525'), br_label('5V_VDDA'))),
            (U.p('16'), br_gnd()),
            # PG also gates the host-VBUS eFuse (hubs sheet, U8 OVLO): PG released = buck regulating = host path off
            (U.p('17'), item(br_part('R', 'R38', 'C25741', VD), br_tp_glabel('TP31', 'PG', 'BUCK_PG')))]
    x0 = U.p('17')[0] - sum(w for _, (w, _) in rows)
    xe = x0 - 10.16
    assert xe >= 15.23, 'buck bank does not fit: xe = %s' % xe
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    hang(s, 'C', 'C58', 'C15849', v18p[0] + 22.86, yt - 15.24)
    s.power('GND', *A.p('65'))
    # --- hub A left: labels to HOST / reset, strap bank
    stub_label(s, A.p('59'), 'USB_UP_DP')
    stub_label(s, A.p('58'), 'USB_UP_DM')
    stub_label(s, A.p('44'), 'HUBA_VBUS_DET')
    stub_label(s, A.p('43'), 'HUB_RESET_N')
    xt = []

    def xtal_a(s, x, y):
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    hang(s, 'R', 'R62', 'C25744', pw7[0] + 17.78, pw7[1])
    hang(s, 'R', 'R75', 'C17168', pw7[0] + 27.94, pw7[1], bottom=('pwr', '3V3'), dnp=True)
    s.wire((pw7[0] + 38.1, pw7[1]), (pw7[0] + 38.1, pw7[1] + 5.08))
    s.label('HUBB_VBUS_DET', pw7[0] + 38.1, pw7[1] + 5.08, 270)
    stub_label(s, B.p('26'), 'HUB_RESET_N')
    # hub B top: 3V3 rail from the left with decoupling (CRFILT / PLLFILT caps are in the left bank)
    ytb = B.p('5')[1]
    yrb = ytb - 10.16
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           fields={'_ref_at': (xU + 2.54, yDM - 5.08), '_val_at': (xU + 2.54, yC1 + 7.62), '_just': 'left'})
    E.y += yDM - E.p('2')[1]
    assert eq(E.p('2'), (xU, yDM)) and eq(E.p('4'), (xU, yC1)), (E.p('2'), E.p('4'))
    stub_label(s, J.p('A7'), 'USB_UP_DM', side='R', n=2)
    stub_label(s, J.p('A6'), 'USB_UP_DP', side='R', n=2)
    stub_label(s, E.p('2'), 'USB_UP_DM', side='L', n=2)
    stub_label(s, E.p('1'), 'USB_UP_DP', side='L', n=2)
    for pin, net in (('7', 'HOST_CC1'), ('6', 'HOST_CC2'), ('10', 'USB_UP_DP'), ('9', 'USB_UP_DM')):
        stub_label(s, E.p(pin), net, side='R', n=1)
    s.wire(J.p('B5'), E.p('5'))
    hang(s, 'R', 'R78', 'C25905', xJ + 22.86, yC2)
    yd = snap(yC2 + 15.24)
    s.wire(J.p('A5'), (xJ + 7.62, yC1), (xJ + 7.62, yd), (xU - 7.62, yd), (xU - 7.62, yC1), E.p('4'))
    hang(s, 'R', 'R77', 'C25905', xJ + 22.86, yd)
    s.label('HOST_CC1', xU - 12.7, yd)                 # named so the ESD array's straight-through pins join it
    s.label('HOST_CC2', xU - 12.7, yC2)
    s.power('GND', *E.p('3'), rot=180)                 # E is mirrored in x: its GND pin points up
    yG, yS = J.p('A1B12')[1], J.p('1')[1]
    s.wire(J.p('A1B12'), (xJ + G, yG), (xJ + G, yS + 5.08))
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    yR = yV - 7.62                                     # rail jogs up over the ESD array (its GND pin points up)
    s.wire(J.p('A4B9'), (xJ + 5.08, yV), (xJ + 5.08, yR), (xr - 5.08, yR), (xr - 5.08, yV), (xr + 45.72, yV))
    s.wire((xr, yV), (xr, yV - 5.08))
    s.label('HOST_VBUS', xr, yV - 5.08, 90)
    vdio(s, 'DZ', 'D40', 'C82323', xr + 12.7, yV)
    hang(s, 'C', 'C74', 'C52923', xr + 30.48, yV)
    r64 = hang(s, 'R', 'R64', 'C25741', xr + 45.72, yV, bottom=None)
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    s.wire(nd, (nd[0] + 20.32, nd[1]))
    t = tp(s, 'TP41', nd[0] + 12.7, nd[1], 0, 'VBUS_DET')
    s.tap(t.p(1))
    s.label('HUBA_VBUS_DET', nd[0] + 20.32, nd[1], 0)
    # --- host-powered mode (2026-11-18, power-design.md "Host-powered mode"): HOST_VBUS -> U8 eFuse -> 5V_BUS
    # while the buck is not regulating (BUCK_PG low: no PD brick, a 5 V-only brick, or soft start); the buck's 5.19 V then reverse-blocks U8
    # and BUCK_PG high (OVLO) turns it off. D41 feeds VIN (the 3V3 buck) from 5V_BUS; R83 bleeds D41's reverse
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    hang(s, 'R', 'R80', 'C25792', xk, r79.p(2)[1], tap=False)
    ne = r79.p(2)
    s.wire(ne, (ne[0] + 7.62, ne[1]))
    s.label('HOST_EN', ne[0] + 7.62, ne[1], 0)
    xi = xk + 25.4 + 63.5                              # IN pin: the strap bank (63.5 wide) sits left of it
    E8 = ic(s, 'TPS259470', 'U8', 'TPS259470ARPWR', 0, 0, 'C3662799',
            fields={'_val_at': (xi + 2.54, yV + 31.75), '_just': 'left'})   # under the body, clear of the GND pin
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    f = flag(s, xk + 12.7, yV)                         # HOST_VBUS is driven from the receptacle
    s.tap(f.p(1))
    hang(s, 'C', 'C78', 'C1525', xk + 22.86, yV)       # 100 n at U8 IN / GND (TI layout guidelines p62)
    stub_label(s, E8.p('1'), 'HOST_EN', side='L')
    rows8 = [(E8.p('2'), br_glabel('BUCK_PG')),                                      # OVLO: the buck's PG
             (E8.p('7'), br_part('C', 'C75', 'C15195')),                              # dVdt 10 n: 0.2 V/ms
             (E8.p('9'), br_part('R', 'R81', 'C270633')),                             # ILM 1.87 k: 1.78 A
             (E8.p('10'), br_part('C', 'C76', 'C47118429'))]                          # ITIMER 5.1 n: 4.3 ms
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    hang(s, 'R', 'R76', 'C25741', rst[0] + 7.62, rst[1])
    t = tp(s, 'TP40', rst[0] + 15.24, rst[1], 0, 'HUB_RESET_N')
    s.tap(t.p(1))
    s.label('HUB_RESET_N', rst[0] + 22.86, rst[1], 0)
    t = tp(s, 'TP42', 27.94, 88.9, 0, 'GND')
    s.power('GND', *t.p(1))
    s.text('Straps (47k to GND): CFG_SEL = 000 / 00 internal default (individual power + OC sense, MTT, '
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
